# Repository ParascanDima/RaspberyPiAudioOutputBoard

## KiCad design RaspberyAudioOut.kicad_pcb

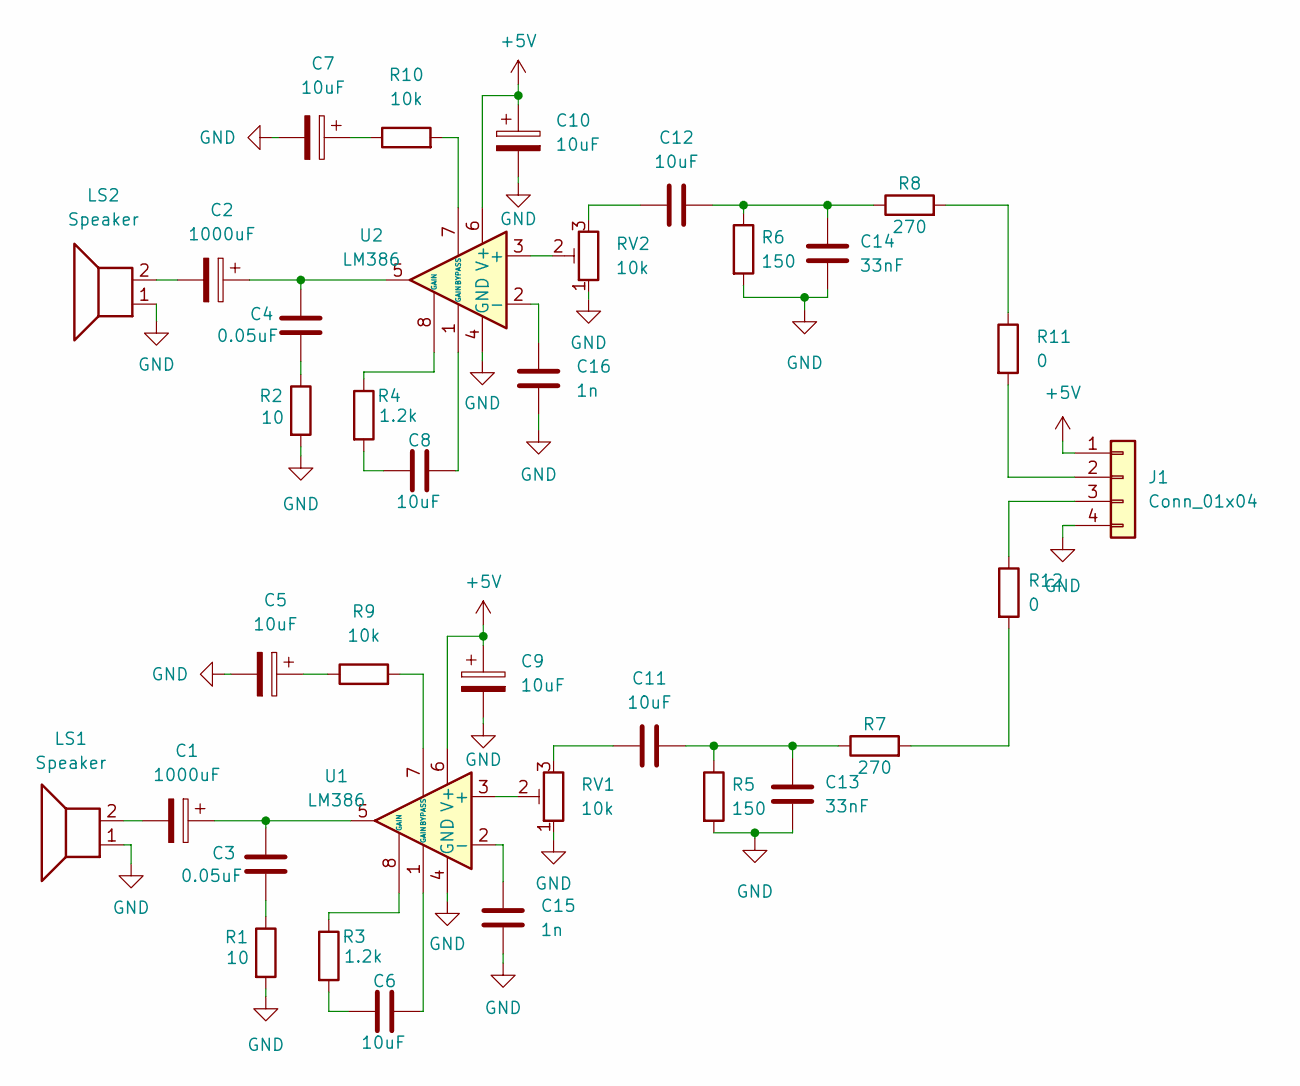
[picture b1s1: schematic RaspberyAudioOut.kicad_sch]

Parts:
C1, C2: 1000uF; CP_Elec_10x10.5
C3, C4: 0.05uF; C_1206_3216Metric
C5, C7, C9, C10: 10uF; CP_Elec_5x5.4
C6, C8, C11, C12: 10uF; C_1206_3216Metric
C13, C14: 33nF; C_0805_2012Metric
C15, C16: 1n; C_0805_2012Metric
J1: Conn_01x04; PinHeader_1x04_P2.54mm_Vertical
LS1, LS2: Speaker; PinSocket_1x02_P2.54mm_Horizontal
R1, R2: 10; R_0805_2012Metric
R3, R4: 1.2k; R_0805_2012Metric
R5, R6: 150; R_0805_2012Metric
R7, R8: 270; R_0805_2012Metric
R9, R10: 10k; R_0805_2012Metric
R11, R12: 0; R_1206_3216Metric_Pad1.30x1.75mm_HandSolder
RV1, RV2: 10k; Potentiometer_Bourns_3386P_Vertical
U1, U2: LM386; SOIC127P600X175-8N

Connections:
+5V: C9.1, C10.1, J1.1, U1.6 (V+), U2.6 (V+)
GND: C5.2, C7.2, C9.2, C10.2, C13.2, C14.2, C15.2, C16.2, J1.4, LS1.1, LS2.1, R1.2, R2.2, R5.2, R6.2, RV1.1, RV2.1, U1.4 (GND), U2.4 (GND)
unnamed: C1.1, C3.2, U1.5
unnamed: C1.2, LS1.2
unnamed: C2.1, C4.2, U2.5
unnamed: C2.2, LS2.2
unnamed: C3.1, R1.1
unnamed: C4.1, R2.1
unnamed: C5.1, R9.1
unnamed: C6.1, R3.2
unnamed: C6.2, U1.1 (GAIN)
unnamed: C7.1, R10.1
unnamed: C8.1, R4.2
unnamed: C8.2, U2.1 (GAIN)
unnamed: C11.1, RV1.3
unnamed: C11.2, C13.1, R5.1, R7.1
unnamed: C12.1, RV2.3
unnamed: C12.2, C14.1, R6.1, R8.1
unnamed: C15.1, U1.2 (-)
unnamed: C16.1, U2.2 (-)
unnamed: J1.2, R11.2
unnamed: J1.3, R12.1
unnamed: R3.1, U1.8 (GAIN)
unnamed: R4.1, U2.8 (GAIN)
unnamed: R7.2, R12.2
unnamed: R8.2, R11.1
unnamed: R9.2, U1.7 (BYPASS)
unnamed: R10.2, U2.7 (BYPASS)
unnamed: RV1.2, U1.3 (+)
unnamed: RV2.2, U2.3 (+)

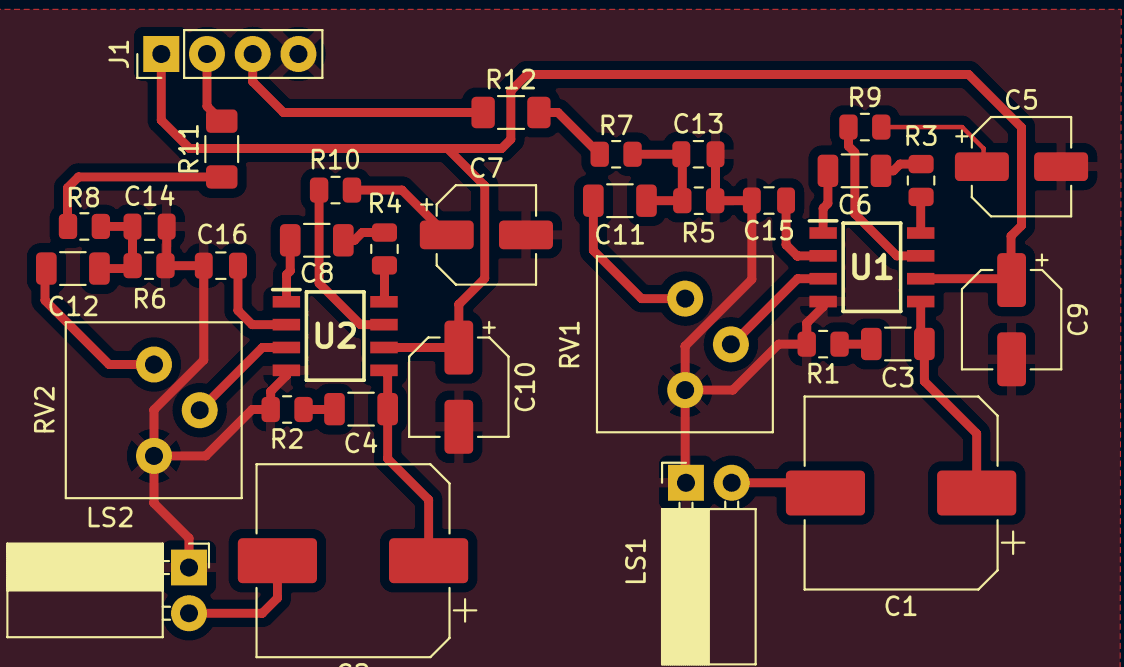
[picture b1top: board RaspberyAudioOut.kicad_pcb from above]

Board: 2 copper layers, 35 parts (0 on the bottom side), 30 nets.

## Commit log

2022-01-25 Finished PCB step1
2022-01-25 Adding libraries
2022-01-26 Adding PDF of PCB
2022-01-26 Changed foot print library paths
2022-02-01 Second step. Changed traces width and some components were added
2022-03-24 Changed tantal to electrolitic output capacitor
